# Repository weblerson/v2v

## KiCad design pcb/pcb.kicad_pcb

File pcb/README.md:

# Placa V2V — ESP32 DevKit v1 + DWM1000 + GY-521

Placa de 2 camadas, **70 × 60 mm**, FR4 1,6 mm, que carrega os três módulos do
protótipo. Todo o mapeamento de pinos vem de `firmware/src/config.h` — ver
`docs/PLAN_DWM1000.md` para as decisões de projeto do firmware.

## Mapeamento

| Sinal | ESP32 (pino do header) | Destino | Camada predominante |
|---|---|---|---|
| `UWB_SCK`  | GPIO18 (9)  | DWM1000 pino 20 (SPICLK)  | B.Cu |
| `UWB_MISO` | GPIO19 (10) | DWM1000 pino 19 (SPIMISO) | B.Cu |
| `UWB_MOSI` | GPIO23 (15) | DWM1000 pino 18 (SPIMOSI) | B.Cu |
| `UWB_CS`   | GPIO5 (8)   | DWM1000 pino 17 (~SPICS)  | B.Cu |
| `UWB_RST`  | GPIO27 (25) | DWM1000 pino 3 (~RST)     | B.Cu |
| `UWB_IRQ`  | GPIO26 (24) | DWM1000 pino 22 (IRQ)     | F.Cu/B.Cu |
| `I2C_SDA`  | GPIO21 (11) | GY-521 SDA                | B.Cu |
| `I2C_SCL`  | GPIO22 (14) | GY-521 SCL                | B.Cu |
| `+3V3`     | pino 3V3 (1) | DWM1000 5/6/7 + C1 + C2  | B.Cu → F.Cu |
| `+5V`      | VIN (30)    | GY-521 VCC                | F.Cu |
| `GND`      | 2 e 29      | plano nas duas faces      | — |

O **DWM1000 é 3,3 V** (máximo absoluto 4,0 V, datasheet Tabela 12). Ele sai do
regulador da própria DevKit, nunca do VIN. O GY-521 fica no 5 V porque tem LDO
próprio a bordo.

## Pontos de atenção na montagem

- **Duas áreas de keep-out de antena** não podem receber cobre, metal, bateria
  ou espaçador — nem por cima nem por baixo. A do DWM1000 está marcada
  `KEEP-OUT` no silk e encosta na borda direita (datasheet §5.1, `d ≥ 10 mm`);
  a do ESP32 fica na ponta inferior do módulo, que projeta 2,5 mm para fora da
  placa de propósito.
- **C2 (100 nF)** é o único capacitor da placa e fica o mais perto possível
  dos pinos 6/7. É o bypass que o datasheet desenha na Figura 9. Nenhum pino
  do módulo é do tipo `PD` (Power Decoupling) — o desacoplamento que o chip
  DW1000 nu exigiria já está dentro do módulo —, então este é o único externo
  necessário. Um bulk adicional foi avaliado e descartado: a DevKit já tem o
  dela na saída do regulador.
- O AMS1117 da DevKit passa a alimentar também o DWM1000 (~0,7 W dissipados).
  Se aparecer brownout, alimente o 3V3 por um regulador externo — brownout se
  parece muito com "o UWB não responde".
- 4 furos M3 (H1–H4) nos cantos + os furos próprios dos módulos.

## Fabricação

`fab/gerbers-v2v-revA.zip` está pronto para enviar. Contém os Gerbers X2 das
9 camadas, os Excellon separados (PTH/NPTH) e os mapas de furação.

- Menor trilha: 0,25 mm · menor isolação: 0,2 mm
- Menor furo: 0,3 mm (vias de sinal) · via padrão 0,6/0,3 mm
- Acabamento/cor: livre (HASL serve)

`fab/pcb-bom.csv` e `fab/pcb-pos.csv` acompanham para a montagem.

## Regerar

```sh
kicad-cli pcb drc --schematic-parity --refill-zones --save-board pcb.kicad_pcb
kicad-cli pcb export gerbers --check-zones --no-protel-ext --subtract-soldermask \
  --layers F.Cu,B.Cu,F.Paste,B.Paste,F.SilkS,B.SilkS,F.Mask,B.Mask,Edge.Cuts \
  -o fab/gerbers pcb.kicad_pcb
kicad-cli pcb export drill --format excellon --excellon-units mm \
  --excellon-separate-th --generate-map --map-format gerberx2 -o fab/gerbers pcb.kicad_pcb
```

As bibliotecas dos módulos estão versionadas em `libs/` com tabelas de projeto
(`fp-lib-table`, `sym-lib-table`), então o projeto abre em qualquer máquina.

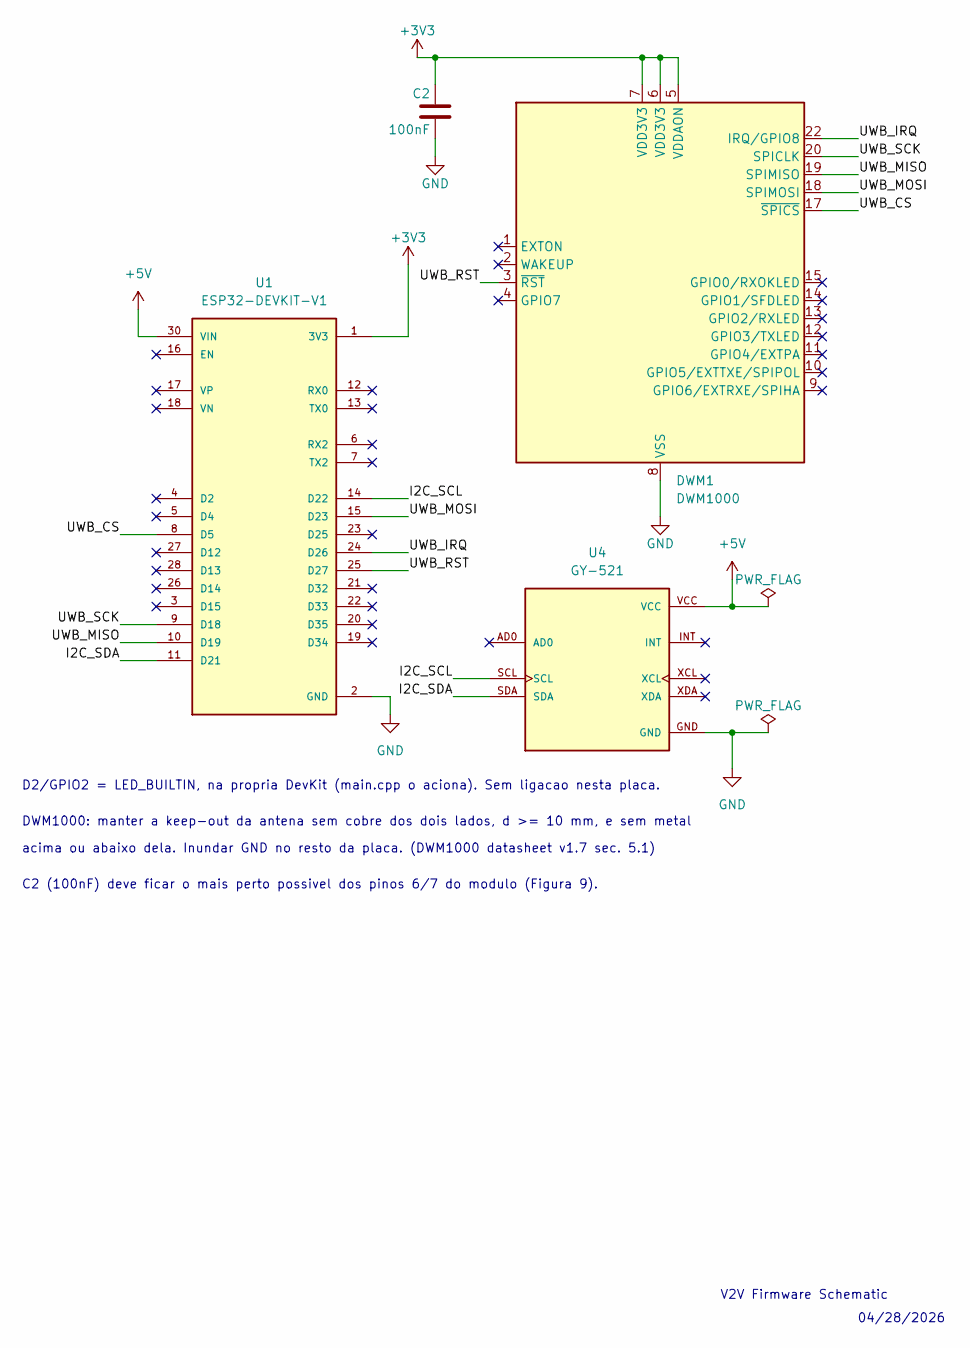
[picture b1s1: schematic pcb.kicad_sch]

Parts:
C2: 100nF; C_0805_2012Metric
DWM1: DWM1000
U1: ESP32-DEVKIT-V1; MODULE_ESP32_DEVKIT_V1; PARTREV N/A
U4: GY-521; MODULE_GY-521; PARTREV NA

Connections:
+3V3: C2.1, DWM1.5 (VDDAON), DWM1.6 (VDD3V3), DWM1.7 (VDD3V3), U1.1 (3V3)
+5V: U1.30 (VIN), U4.VCC
/I2C_SCL: U1.14 (D22), U4.SCL
/I2C_SDA: U1.11 (D21), U4.SDA
/UWB_CS: DWM1.17 (~SPICS), U1.8 (D5)
/UWB_IRQ: DWM1.22 (IRQ/GPIO8), U1.24 (D26)
/UWB_MISO: DWM1.19 (SPIMISO), U1.10 (D19)
/UWB_MOSI: DWM1.18 (SPIMOSI), U1.15 (D23)
/UWB_RST: DWM1.3 (~RST), U1.25 (D27)
/UWB_SCK: DWM1.20 (SPICLK), U1.9 (D18)
GND: C2.2, DWM1.8 (VSS), DWM1.16 (VSS), DWM1.21 (VSS), DWM1.23 (VSS), DWM1.24 (VSS), U1.2 (GND), U1.29 (GND), U4.GND

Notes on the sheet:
V2V Firmware Schematic
04/28/2026
D2/GPIO2 = LED_BUILTIN, na propria DevKit (main.cpp o aciona). Sem ligacao nesta placa.
DWM1000: manter a keep-out da antena sem cobre dos dois lados, d >= 10 mm, e sem metal
acima ou abaixo dela. Inundar GND no resto da placa. (DWM1000 datasheet v1.7 sec. 5.1)
C2 (100nF) deve ficar o mais perto possivel dos pinos 6/7 do modulo (Figura 9).

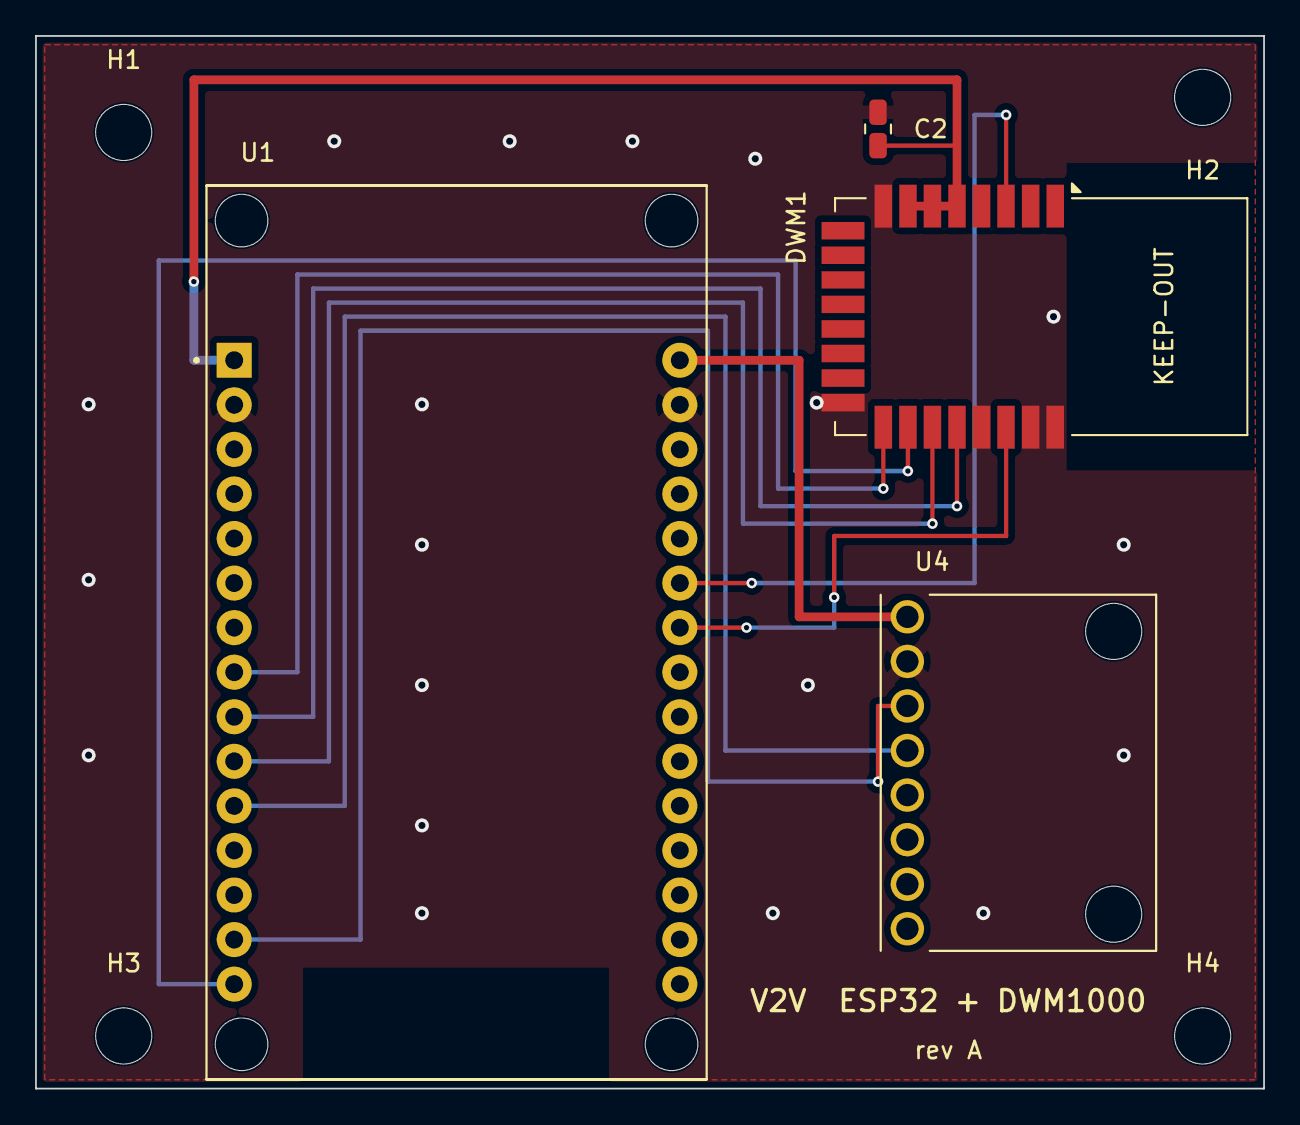
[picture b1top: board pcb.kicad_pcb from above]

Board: 2 copper layers, 70.0 x 60.0 mm, 8 parts (0 on the bottom side), 11 nets.

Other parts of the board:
H1, H2, H3, H4: MountingHole_3.2mm_M3

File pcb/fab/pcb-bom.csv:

"Refs","Valor","Footprint","Qtd"
"C2","100nF","Capacitor_SMD:C_0805_2012Metric","1"
"DWM1","DWM1000","RF_Module:DWM1000","1"
"U1","ESP32-DEVKIT-V1","esp32:MODULE_ESP32_DEVKIT_V1","1"
"U4","GY-521","gy-521:MODULE_GY-521","1"

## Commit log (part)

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2026-03-15 first configuration of esp now
2026-03-24 implementação do MPU6050
2026-04-08 movendo para PlatformIO
2026-04-12 primeiro algoritmo de posição e declaração do monolito
2026-04-12 implementação do monitor
2026-04-12 implementação da interface dispositivo/monitor no firmware
2026-04-22 Metricas
2026-04-30 footprints
2026-06-04 melhoria na documentação e funcionamento do radar
